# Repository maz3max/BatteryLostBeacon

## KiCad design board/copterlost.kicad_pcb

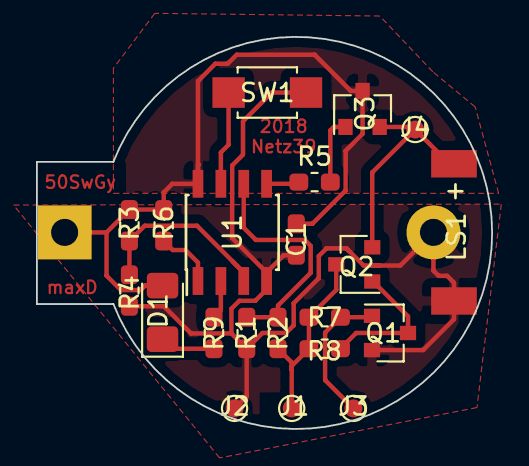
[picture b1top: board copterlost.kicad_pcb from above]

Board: 2 copper layers, 25.3 x 21.8 mm, 22 parts (1 on the bottom side), 14 nets.

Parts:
BT1: Battery_Cell; BatteryHolder_Keystone_104_1x23mm
C1: 0.1uF; C_0603_1608Metric_Pad1.05x0.95mm_HandSolder
D1: LED; LED_1206_3216Metric_Pad1.42x1.75mm_HandSolder
J1: 5V_Copter; TestPoint_Pad_D1.0mm
J2: Ground; TestPoint_Pad_D1.0mm
J3: FC.Beeper-; TestPoint_Pad_D1.0mm
J4: FC.Beeper+; TestPoint_Pad_D1.0mm
LS1: Speaker; Beeper
Q1, Q2, Q3: MMBT3904; SOT-23
R1, R4, R8: 5.1k; R_0603_1608Metric_Pad1.05x0.95mm_HandSolder
R2, R6, R7: 10k; R_0603_1608Metric_Pad1.05x0.95mm_HandSolder
R3: 18k; R_0603_1608Metric_Pad1.05x0.95mm_HandSolder
R5: 330; R_0603_1608Metric_Pad1.05x0.95mm_HandSolder
R9: 47; R_0603_1608Metric_Pad1.05x0.95mm_HandSolder
SW1: SW_Push; SW_SPST_B3U-1000P
U1: ATTINY13-20SSU; SOIC-8_3.9x4.9mm_P1.27mm

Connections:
+5V: J1.1, Q2.3, R1.1, R7.1, R8.1
+BATT: BT1.1, C1.1, D1.2, Q3.3, R3.1, R6.2, U1.8
/Batt-Sense: R3.2, R4.1, U1.3
/Beeper: Q3.1, R5.2
/Button: SW1.1, U1.7
/LED: R9.1, U1.2
/Sense: R1.2, R2.1, U1.6
/Speaker: J4.1, LS1.1, Q2.2, Q3.2
GND: BT1.2, C1.2, J2.1, LS1.2, Q1.2, R2.2, R4.2, SW1.2, U1.4
unnamed: D1.1, R9.2
unnamed: J3.1, Q1.1, R7.2
unnamed: Q1.3, Q2.1, R8.2
unnamed: R5.1, U1.5
unnamed: R6.1, U1.1

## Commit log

2018-07-18 finally got it working
2018-07-18 more clean startup sound
2018-07-18 add kicad files for board
2018-07-20 more responsive button handling
2018-07-20 slow down main clock to reduce power usage
2018-08-11 migrate to kicad 5 & new layout
2018-08-12 squeeze to smaller layout
2018-08-12 add battery warning
2018-08-12 enable internal pull-up
2018-08-12 ready to etch
2018-08-13 some fixes for new design
2018-08-13 some layout fixes
2018-08-13 working version
